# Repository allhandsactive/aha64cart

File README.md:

## Simple64Cart: AHA Edition ##

This is a modified version of [Simple64Cart](https://github.com/go4retro/Simple64Cart) with the following changes.
* Moved ROM socket slightly to the left so it no longer is pushing up against the board edge
* Allow the use of 16k cart images.
* Allow select one of four 16k banks in the 64k ROM by changing A14 and A15 values via jumpers.

### Jumper Settings ###

##### A14/A15 #####

Jumpers A14 and A15  allow selecting one of four banks in the 64k ROM. This will allow you to program up to four ROM images in an select which one you wish to boot when the computer starts up.

|   Memory    | A14    | A15    |
| ------------|--------|--------|
|0x0000-0x3fff| closed | closed |
|0x4000-0x7fff| open   | closed |
|0x8000-0xbfff| closed | open   |
|0xC000-0xffff| open   | open   |

##### EXROM/GAME #####

These two jumpers /EXROM and /GAME control which memory mapping the C64 uses when mapping your ROM into memory.

There are 3 types of cartridges, 8k, 16k and Ultimax (16k). The two different 16k mappings place the upper 8k at different locations in memory. The main 16k mode will place it at 0xA000 overwriting the basic ROM and Ultimax mode will place it at 0xE000 overwriting the kernel ROM. The lower 8k is always mapped into 0x8000.

The Ultimax mapping is for compatibility with the Japanese Commodore "MAX" computers.

| Mapping                                       | /GAME  | /EXROM |
|-----------------------------------------------|--------|--------|
|  None                                         | open   | open   |
| 8k  (0x8000-0x9 fff)                          | open   | closed |
| 16k (Ultimax) (0x8000-0x9fff),(0xe000-0xffff) | closed | open   |
| 16k (0x8000-0x9fff),(0xa000-0xbfff)           | closed | closed |

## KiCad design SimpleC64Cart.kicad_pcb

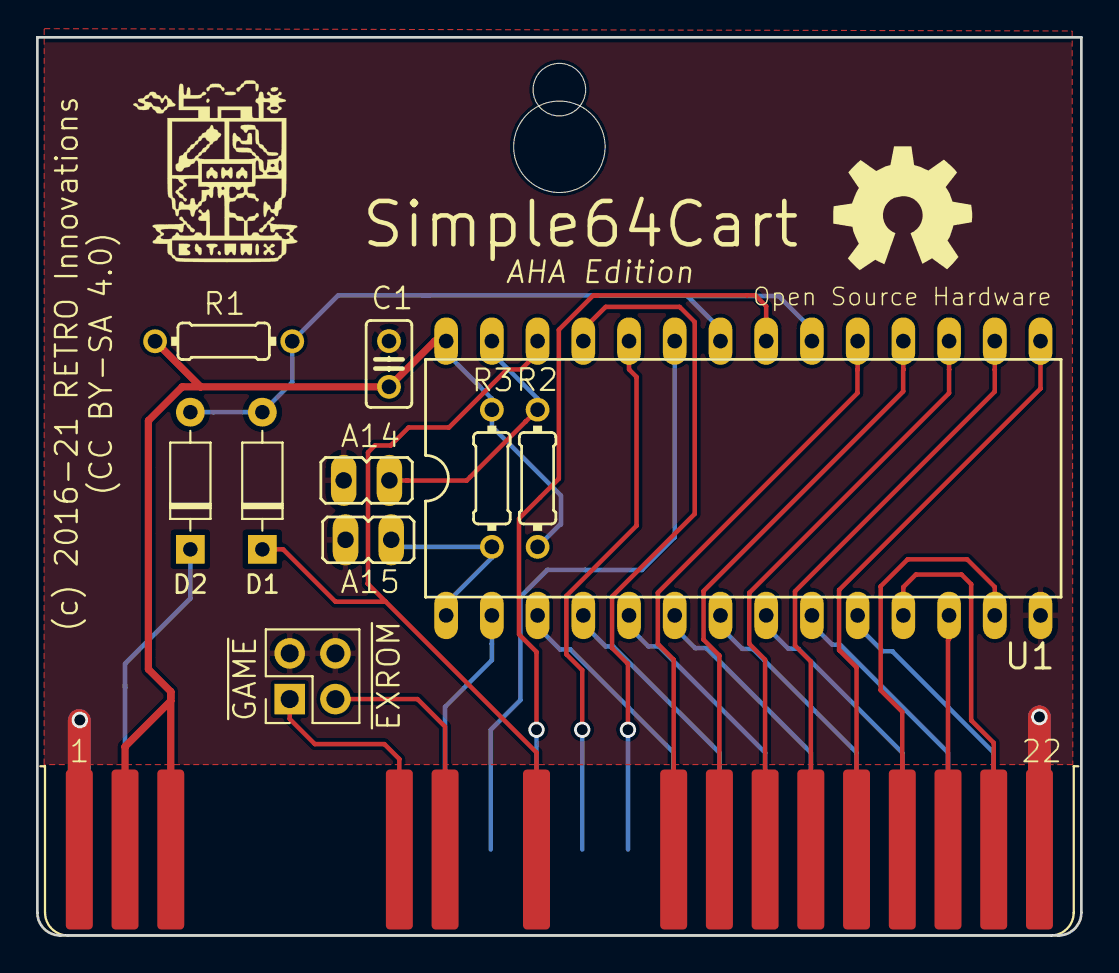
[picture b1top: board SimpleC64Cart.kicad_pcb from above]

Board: 2 copper layers, 58.0 x 49.9 mm, 13 parts (0 on the bottom side), 30 nets.

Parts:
A14, A15: Conn_01x02_Male; JP1
C1: 0.1uf; C025-025X050
CART: CARTRIDGE_C64
D1, D2: D_Small; D_DO-35_SOD27_P7.62mm_Horizontal
GOLD_ORB_SM1: Open Source Hardware; OSHW_8MM
J1: TYPE; PinHeader_2x02_P2.54mm_Vertical
R1, R2, R3: 10k; 0204_7
U1: 27512G; DIL28-6
X1: EXPANSION_PORT_C64_EDGE; MA100-22-2

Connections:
/A0: U1.10, X1.Y
/A1: U1.9, X1.X
/A2: U1.8, X1.W
/A3: U1.7, X1.V
/A4: U1.6, X1.U
/A5: U1.5, X1.T
/A6: U1.4, X1.S
/A7: U1.3, X1.R
/A8: U1.25, X1.P
/A9: U1.24, X1.N
/A10: U1.21, X1.M
/A11: U1.23, X1.L
/A12: U1.2, X1.K
/D0: U1.11, X1.21
/D1: U1.12, X1.20
/D2: U1.13, X1.19
/D3: U1.15, X1.18
/D4: U1.16, X1.17
/D5: U1.17, X1.16
/D6: U1.18, X1.15
/D7: U1.19, X1.14
/~EXROM: J1.3, X1.9
/~GAME: J1.1, X1.8
/~ROMH: D2.1, X1.B
/~ROML: D1.1, U1.26, X1.11
GND: A14.1, A15.1, C1.2, J1.2, J1.4, U1.14, X1.1, X1.22, X1.A, X1.Z
unnamed: A14.2, R2.2, U1.27
unnamed: A15.2, R3.2, U1.1
unnamed: D1.2, D2.2, R1.2, U1.20, U1.22
VCC: C1.1, R1.1, R2.1, R3.1, U1.28, X1.2, X1.3

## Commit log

2021-04-24 Lengthen board by 1 mm
2021-04-24 Add generated gerber files
2021-04-25 Modified pcb layout.
    * support 16k rom images
    * jumpers allow using 1 of 4 16k banks
2021-04-25 Update gerbers
2021-04-25 Add BOM Files
2021-04-27 add license
    yeet
2021-05-01 Add README
2021-05-04 added unmodified c64 cart from thingiverse, and added a switch adapter to use switches instead of jumpers
2021-05-05 updated switch adapter dimensions
2021-06-03 Add schematic for board layout

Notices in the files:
SimpleC64Cart.kicad_pcb:
(c) 2016-21 RETRO Innovations
(CC BY-SA 4.0)
